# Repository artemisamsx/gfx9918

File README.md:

# Artemisa MSX - GFX9918 Graphics Card

This repository contains the KiCad project files for the GFX9918 graphics card.

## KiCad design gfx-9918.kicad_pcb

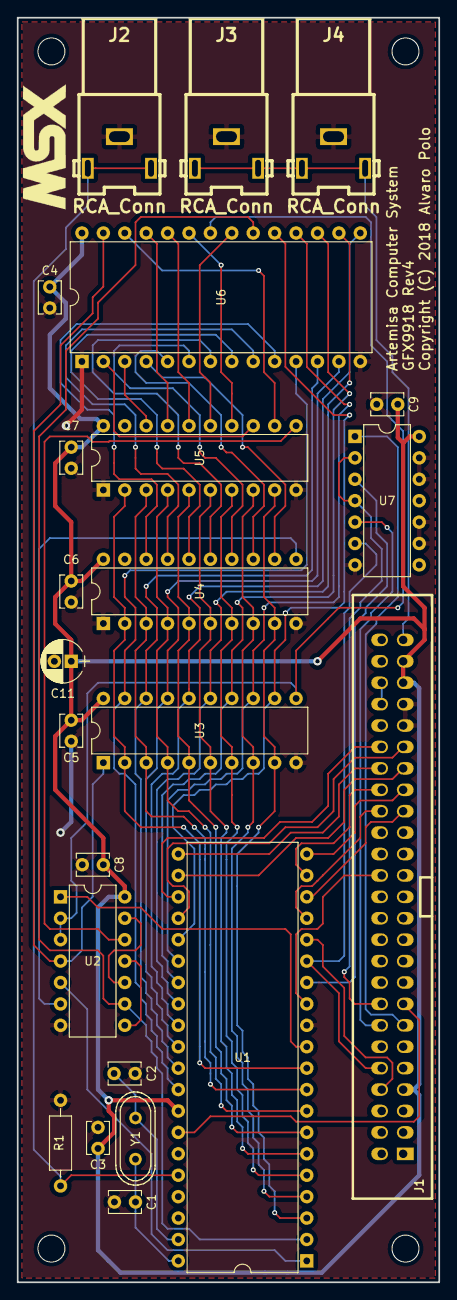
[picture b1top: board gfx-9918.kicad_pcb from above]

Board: 2 copper layers, 50.0 x 150.0 mm, 23 parts (0 on the bottom side), 62 nets.

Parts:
C1, C2: 56pF; Disc_capacitor
C3, C4, C5, C6, C7, C8, C9: 100nF; Disc_capacitor
C11: 10uF; Radial_capacitor
J1: GFX_Connector_Input; GFX_conn
J2: RCA_Conn; RCA_yellow
J3: RCA_Conn; RCA_white
J4: RCA_Conn; RCA_red
R1: 470; Axial_resistor
U1: TMS9918; DIP-40_600
U2: 74HCT04; DIP-14_300
U3, U4, U5: 74HCT574; DIP-20_300
U6: 62256; DIP-28_600
U7: 74HC32; DIP-14_300
Y1: 10.7386Mhz; Crystal

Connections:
/Card connector & power/A0: J1.28, U1.13
/Card connector & power/BUSDIR: J1.10, U1.15, U7.6
/Card connector & power/DATA0: J1.34, U1.17
/Card connector & power/DATA1: J1.33, U1.18
/Card connector & power/DATA2: J1.36, U1.19
/Card connector & power/DATA3: J1.35, U1.20
/Card connector & power/DATA4: J1.38, U1.21
/Card connector & power/DATA5: J1.37, U1.22
/Card connector & power/DATA6: J1.40, U1.23
/Card connector & power/DATA7: J1.39, U1.24
/Card connector & power/SOUNDOUT: J1.49, J3.1, J4.1
/Card connector & power/~INT: J1.8, U1.16
/Card connector & power/~RD: J1.14, U7.5
/Card connector & power/~RESET: J1.15, U1.34
/Card connector & power/~VDPIOSL: J1.16, U7.2, U7.4
/Card connector & power/~WR: J1.13, U7.1
/Interface Decoding Logic/~CSW: U1.14, U7.3
/Output connectors/CVBS: J2.1, R1.1, U1.36
/VRAM Decoding Logic/A0: U4.18, U6.10
/VRAM Decoding Logic/A1: U4.17, U6.9
/VRAM Decoding Logic/A2: U4.16, U6.8
/VRAM Decoding Logic/A3: U4.15, U6.7
/VRAM Decoding Logic/A4: U4.14, U6.6
/VRAM Decoding Logic/A5: U4.13, U6.5
/VRAM Decoding Logic/A6: U4.12, U6.4
/VRAM Decoding Logic/A7: U5.18, U6.3
/VRAM Decoding Logic/A8: U5.17, U6.25
/VRAM Decoding Logic/A9: U5.16, U6.24
/VRAM Decoding Logic/A10: U5.15, U6.21
/VRAM Decoding Logic/A11: U5.14, U6.23
/VRAM Decoding Logic/A12: U5.13, U6.2
/VRAM Decoding Logic/A13: U5.12, U6.26
/VRAM Decoding Logic/AD0: U1.10, U3.2, U4.2, U5.2
/VRAM Decoding Logic/AD1: U1.9, U3.3, U4.3, U5.3
/VRAM Decoding Logic/AD2: U1.8, U3.4, U4.4, U5.4
/VRAM Decoding Logic/AD3: U1.7, U3.5, U4.5, U5.5
/VRAM Decoding Logic/AD4: U1.6, U3.6, U4.6, U5.6
/VRAM Decoding Logic/AD5: U1.5, U3.7, U4.7, U5.7
/VRAM Decoding Logic/AD6: U1.4, U3.8, U4.8, U5.8
/VRAM Decoding Logic/AD7: U1.3, U3.9, U4.9, U5.9
/VRAM Decoding Logic/RD: U2.4, U3.1, U6.27
/VRAM Decoding Logic/WR: U2.2, U2.3, U3.11, U6.22
/VRAM Decoding Logic/~CAS: U1.2, U2.9, U6.20
/VRAM Decoding Logic/~RAS: U1.1, U2.5
/VRAM Decoding Logic/~WR: U1.11, U2.1
/VRAM/RD0: U1.32, U3.19, U6.11
/VRAM/RD1: U1.31, U3.18, U6.12
/VRAM/RD2: U1.30, U3.17, U6.13
/VRAM/RD3: U1.29, U3.16, U6.15
/VRAM/RD4: U1.28, U3.15, U6.16
/VRAM/RD5: U1.27, U3.14, U6.17
/VRAM/RD6: U1.26, U3.13, U6.18
/VRAM/RD7: U1.25, U3.12, U6.19
GND: C1.2, C2.2, C3.2, C4.2, C5.2, C6.2, C7.2, C8.2, C9.2, C11.2, J1.41, J1.43, J2.2, J3.2, J4.2, R1.2, U1.12, U2.7, U3.10, U4.1, U4.10, U5.1, U5.10, U6.1, U6.14, U7.7, U7.9, U7.10, U7.12, U7.13
unnamed: C1.1, U1.40, Y1.1
unnamed: C2.1, U1.39, Y1.2
unnamed: J1.44, J1.46
unnamed: U2.6, U4.11
unnamed: U2.10, U2.13
unnamed: U2.8, U2.11
unnamed: U2.12, U5.11
~: C3.1, C4.1, C5.1, C6.1, C7.1, C8.1, C9.1, C11.1, J1.7, J1.45, J1.47, U1.33, U2.14, U3.20, U4.20, U5.20, U6.28, U7.14

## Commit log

2018-10-25 Complete GFX-9918 schematic
2018-10-26 Complete GFX-9918 PCB
2018-10-26 Make so aesthetic changes to GFX-9918
2018-10-27 Remove traces of ArteMSX in hardware files
2018-11-10 Take `SOUNDOUT` from GFX input in schematics
2018-11-10 Take `SOUNDOUT` from GFX input in PCB
2019-03-22 Fix power pin arrangement in GFX9918
    For discrete logic symbols, add a new one to represent the power connections. So we can represent them in the schematic explicitely.
    This also fixes the different format in capacitor values.
2019-03-24 Fix wrong pin layout of RCA connector footprints
2019-03-25 Fix missing footprint 3D models
    Even add a custom one for the MSX slot connector.
2019-04-15 Add PCB design for PS2 Keyboard Adapter
2019-05-07 Fix board dimensions and plot rev01 of motherboard
2019-07-15 Increase width of power tracks in GFX9918
2019-09-02 [gfx9918] Bump to rev 3
2019-09-04 [gfx9918] Fix missing symbol HM62256
2019-09-04 [gfx9918] Fix capacitor values for clock circuit
2019-09-05 [gfx9918] Set board settings to match JCLPCB design rules
2019-09-05 Update changelogs and revision numbers of all PCBs
2019-09-05 Fix changelog files to reflect unreleased changes
2019-11-11 Fix background color issues by unconnecting EXTVDP pin
2019-11-12 Bump gfx9918 to rev4
2020-05-17 Reorganize GFX9918 into sheets
2021-03-22 Use libs from kicadlibs repository
2021-03-22 Add README and LICENSE files
2021-04-15 Update to latest libs to use power connectors in first part for multipart symbols
2022-04-28 Upgrade project files to KiCad 6
2022-04-28 Remove and ignore local and cache files

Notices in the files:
gfx-9918.kicad_pcb:
Copyright (C) 2018 Alvaro Polo
